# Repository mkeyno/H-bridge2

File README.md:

# H-bridge2
this is H-bridge circuit to operate under 12-24 input voltage, with parallel mosfet and push-pull gate driver
##schematic of last change 

##PCB

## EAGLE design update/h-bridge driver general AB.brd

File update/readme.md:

new updated file has been added

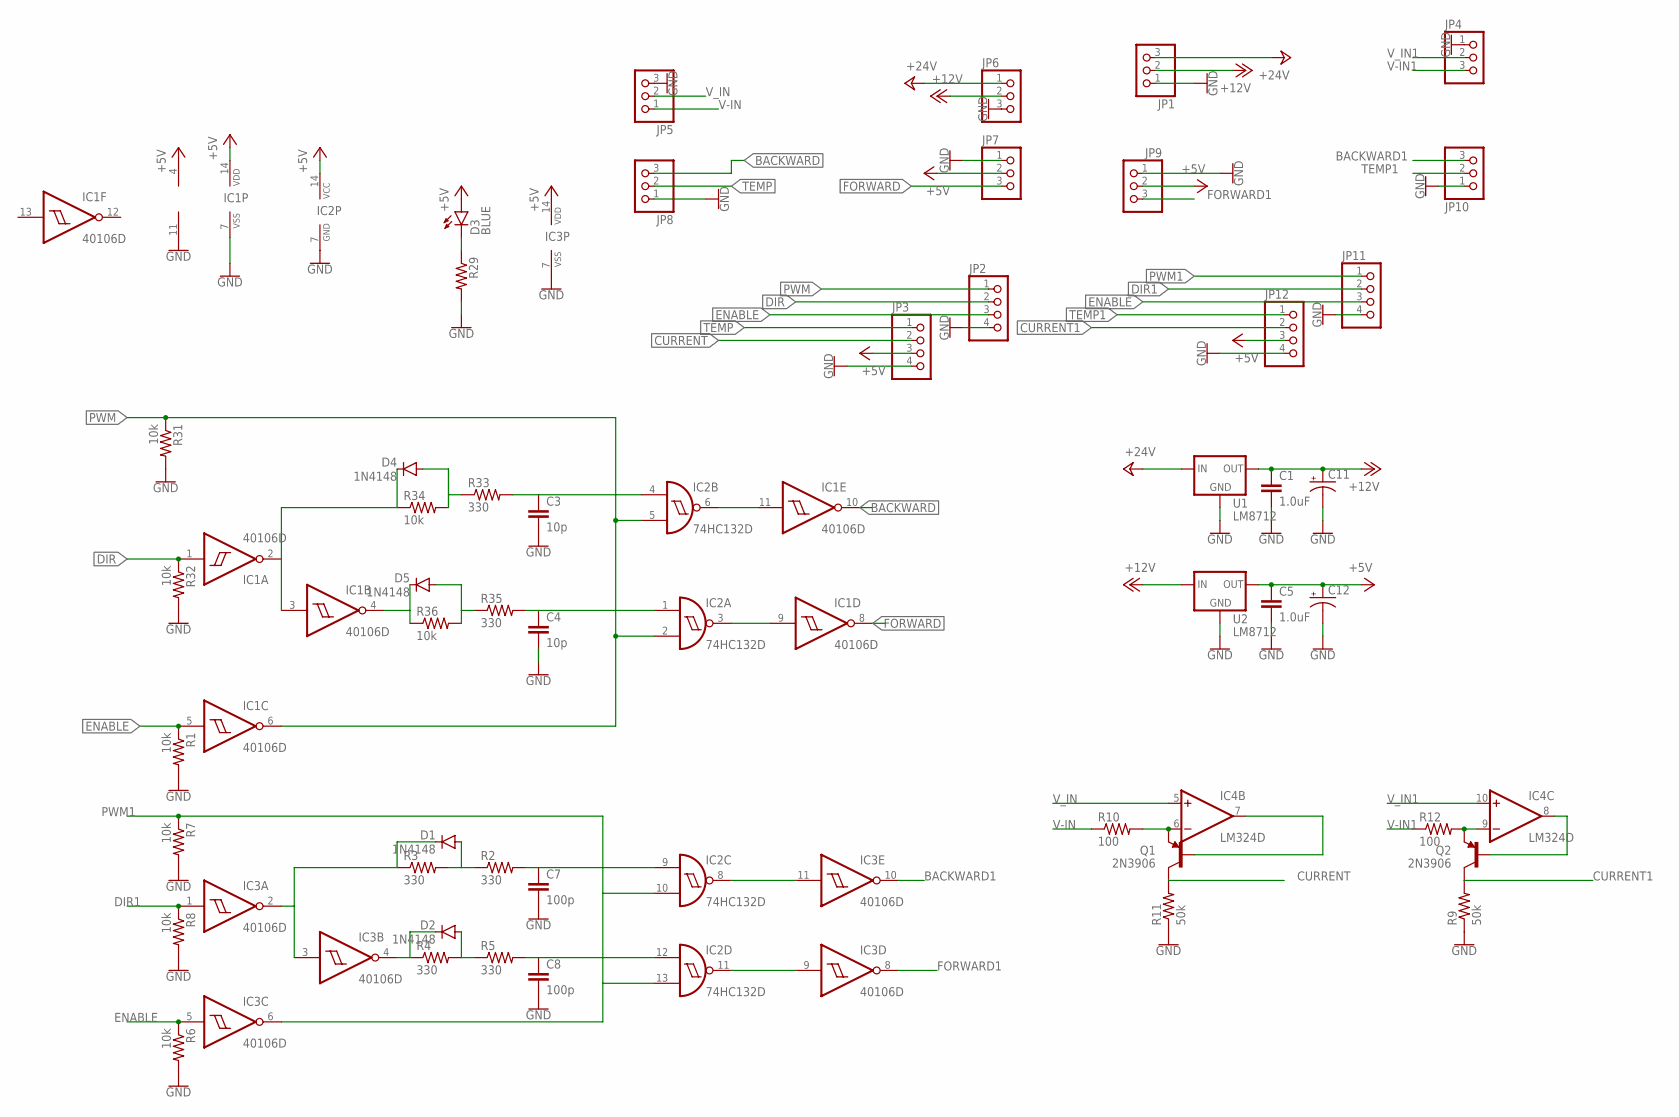
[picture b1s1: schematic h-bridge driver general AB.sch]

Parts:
C1, C5: 1.0uF; 1206
C3, C4: 10p; 0805-CAP
C7, C8: 100p; 0805-CAP
C11, C12: CAP_POLPTH4; CPOL-RADIAL-1000UF-25V
D1, D2, D4, D5: 1N4148; SOD-123
D3: BLUE; LED-1206
IC1, IC3: 40106D; SO14
IC2: 74HC132D; SO14
IC4: LM324D; SO14
JP1, JP4, JP5, JP6, JP7, JP8, JP9, JP10: PINHD-1X3; 1X03
JP2, JP3, JP11, JP12: PINHD-1X4; 1X04
Q1, Q2: 2N3906; SOT23-3
R1, R6, R7, R8, R31, R32, R34, R36: 10k; 0805
R2, R3, R4, R5, R33, R35: 330; 0805
R9, R11: 50k; 0805
R10, R12: 100; 0805
R29: 0.3OHM-1/8W-1%(0805); 0805
U1, U2: LM8712; 78XXL

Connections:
+5V: C5.1, C12.+, D3.A, IC1.14 (VDD), IC2.14 (VCC), IC3.14 (VDD), IC4.4 (V+), JP3.3, JP7.2, JP9.2, JP12.3, U2.OUT
+12V: C1.1, C11.+, JP1.2, JP6.2, U1.OUT, U2.IN
+24V: JP1.3, JP6.1, U1.IN
BACKWARD: IC1.10 (O), JP8.3
BACKWARD1: IC3.10 (O), JP10.3
CURRENT: JP3.2, Q1.3 (C), R11.2
CURRENT1: JP12.2, Q2.3 (C), R9.2
DIR: IC1.1 (I), JP2.2, R32.1
DIR1: IC3.1 (I), JP11.2, R8.1
ENABLE: IC1.5 (I), IC3.5 (I), JP2.3, JP11.3, R1.1, R6.1
FORWARD: IC1.8 (O), JP7.3
FORWARD1: IC3.8 (O), JP9.3
GND: C1.2, C3.2, C4.2, C5.2, C7.2, C8.2, C11.-, C12.-, IC1.7 (VSS), IC2.7 (GND), IC3.7 (VSS), IC4.11 (V-), JP1.1, JP2.4, JP3.4, JP4.1, JP5.3, JP6.3, JP7.1, JP8.1, JP9.1, JP10.1, JP11.4, JP12.4, R1.2, R6.2, R7.2, R8.2, R9.1, R11.1, R29.2, R31.2, R32.2, U1.GND, U2.GND
unnamed: IC1.11 (I), IC2.6 (O)
unnamed: IC1.9 (I), IC2.3 (O)
unnamed: IC2.8 (O), IC3.11 (I)
unnamed: IC2.11 (O), IC3.9 (I)
unnamed: C7.1, IC2.9 (I0), R2.2
unnamed: D3.C, R29.1
unnamed: D1.A, R2.1, R3.2
unnamed: D1.C, IC3.2 (O), IC3.3 (I), R3.1
unnamed: IC4.6 (-IN), Q1.2 (E), R10.2
unnamed: D2.C, IC3.4 (O), R4.1
unnamed: D2.A, R4.2, R5.1
unnamed: C8.1, IC2.12 (I0), R5.2
unnamed: IC4.7 (OUT), Q1.1 (B)
unnamed: IC4.9 (-IN), Q2.2 (E), R12.2
unnamed: IC4.8 (OUT), Q2.1 (B)
unnamed: D4.C, IC1.2 (O), IC1.3 (I), R34.1
unnamed: D4.A, R33.1, R34.2
unnamed: C3.1, IC2.4 (I0), R33.2
unnamed: C4.1, IC2.1 (I0), R35.2
unnamed: D5.A, R35.1, R36.2
unnamed: D5.C, IC1.4 (O), R36.1
PWM: IC1.6 (O), IC2.2 (I1), IC2.5 (I1), JP2.1, R31.1
PWM1: IC2.10 (I1), IC2.13 (I1), IC3.6 (O), JP11.1, R7.1
TEMP: JP3.1, JP8.2
TEMP1: JP10.2, JP12.1
V-IN: JP5.1, R10.1
V-IN1: JP4.3, R12.1
V_IN: IC4.5 (+IN), JP5.2
V_IN1: IC4.10 (+IN), JP4.2

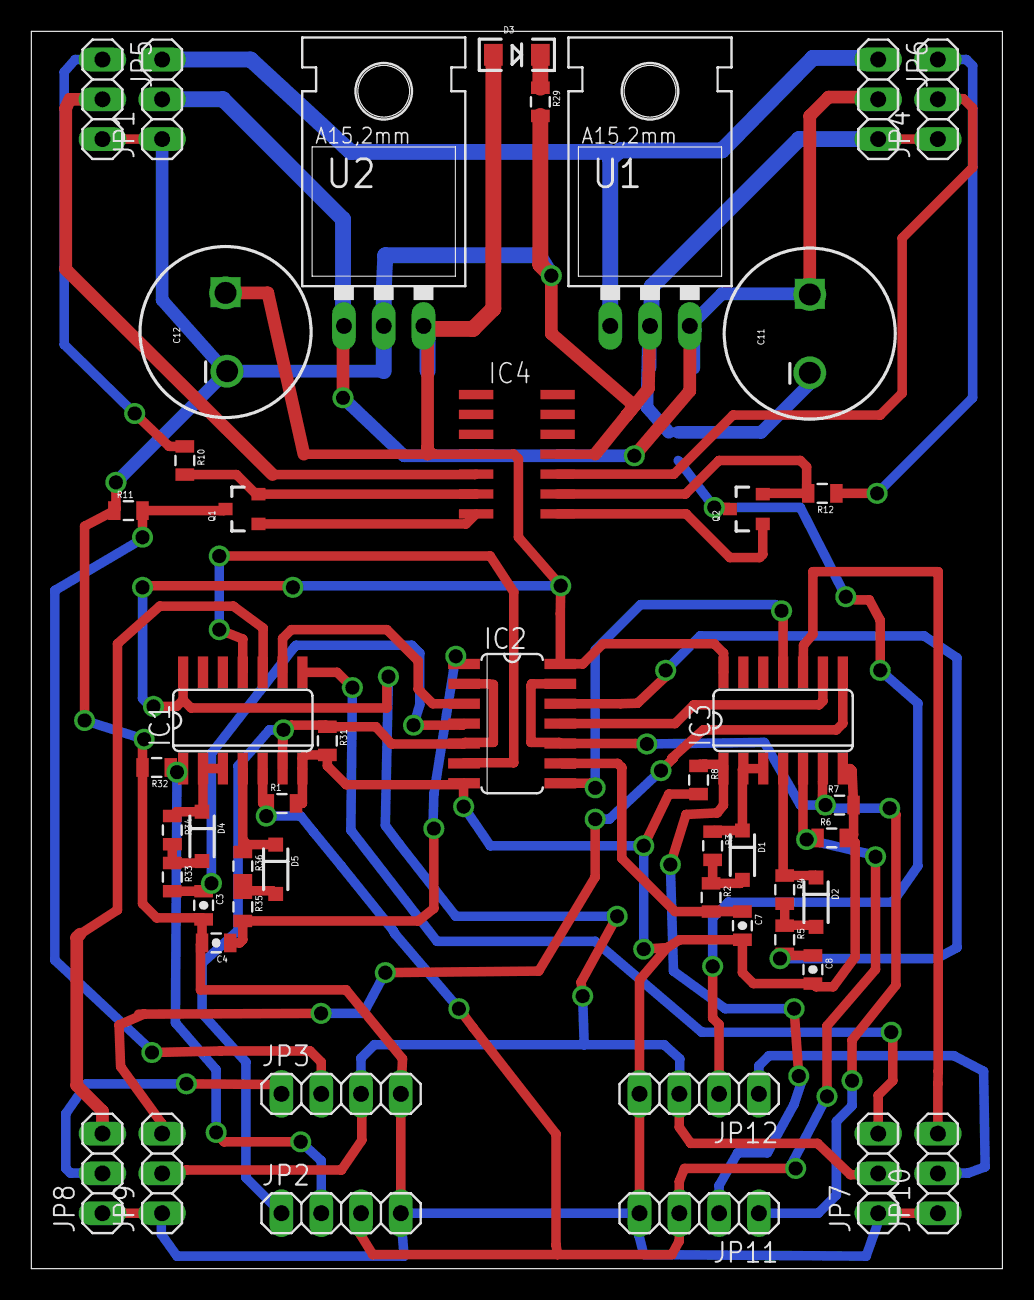
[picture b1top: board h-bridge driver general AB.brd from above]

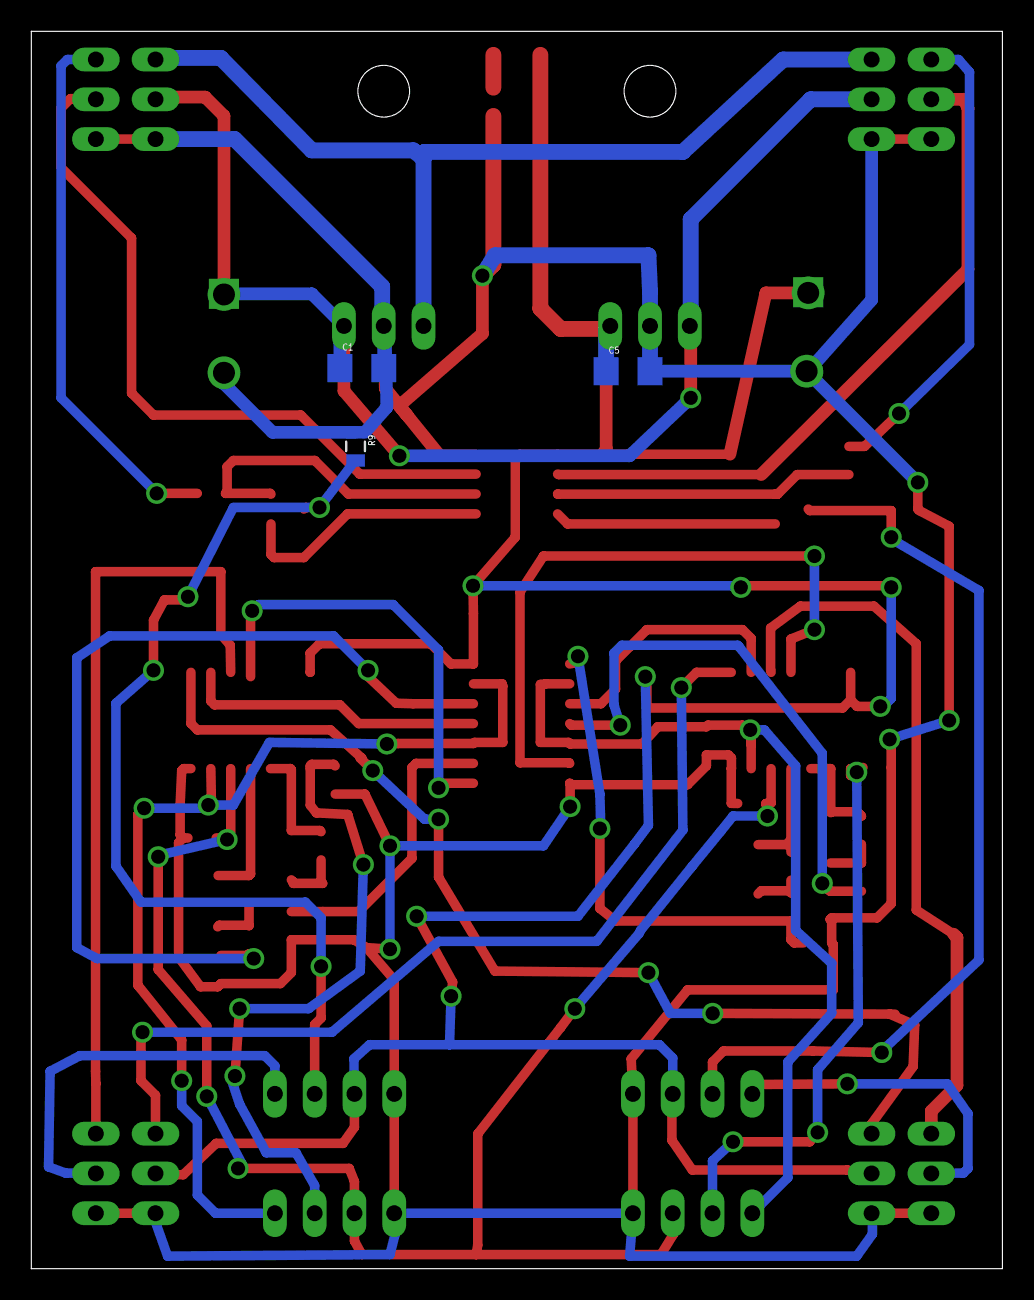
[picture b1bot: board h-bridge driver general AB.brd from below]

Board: 2 copper layers, 62.0 x 79.0 mm, 52 parts (3 on the bottom side), 42 nets.

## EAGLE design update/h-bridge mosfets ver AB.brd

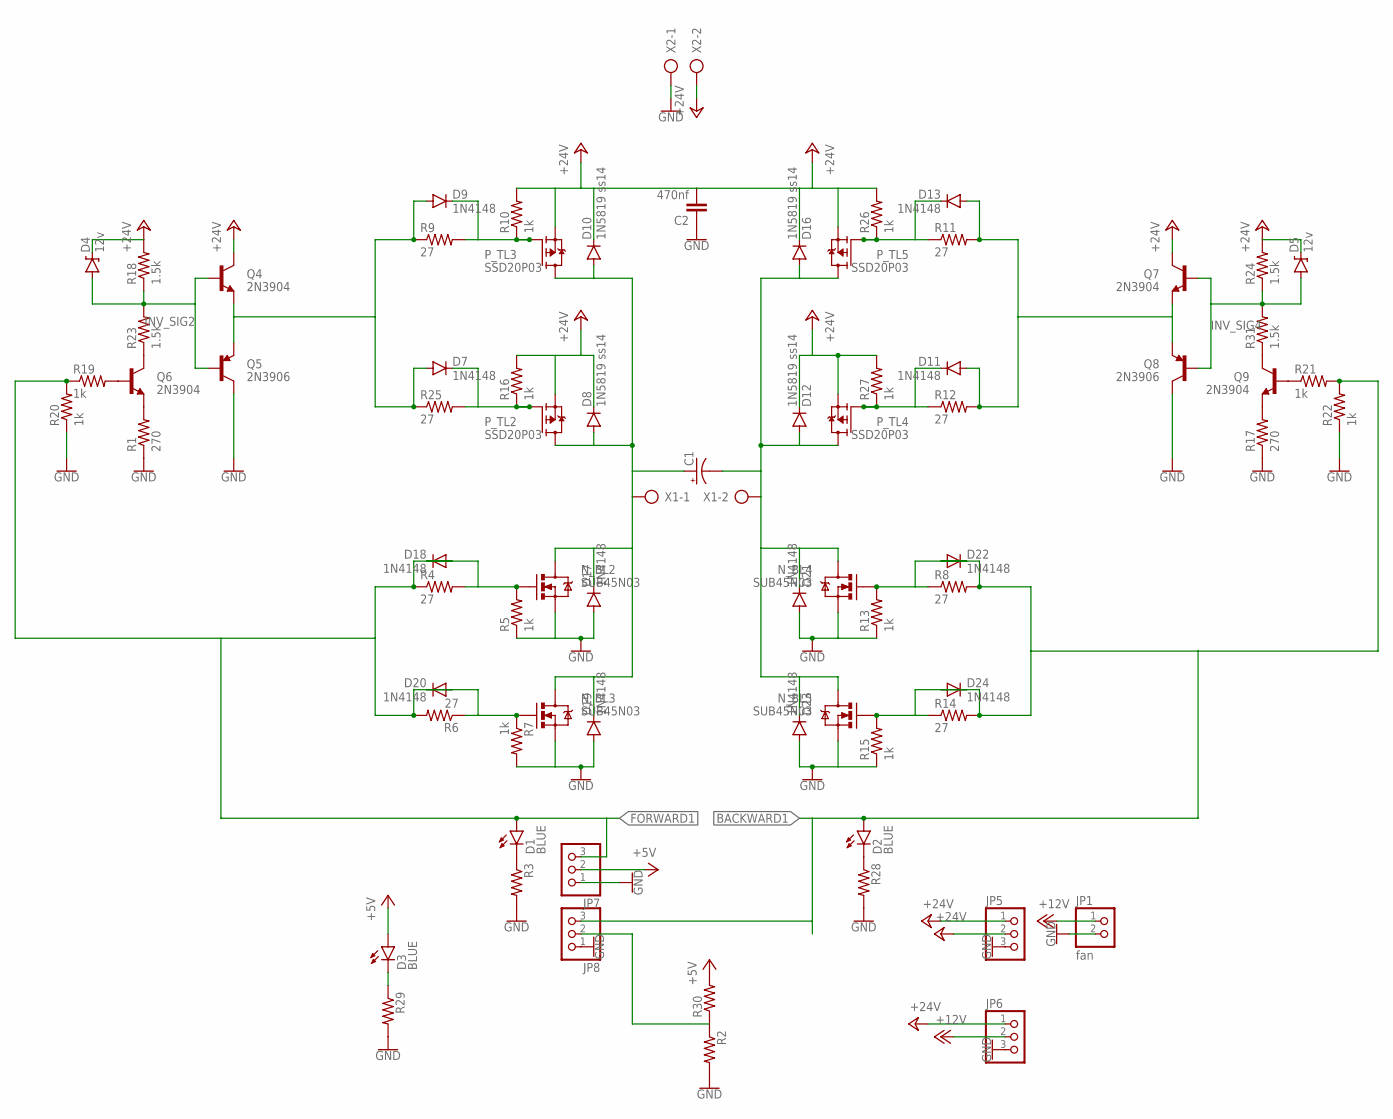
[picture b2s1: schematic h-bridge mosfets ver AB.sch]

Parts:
C1: 1000UF-25V(PTH); CPOL-RADIAL-1000UF-25V
C2: 470nf; 1206
D1, D2, D3: BLUE; LED-1206
D4, D5: 12v; SMB-DIODE
D7, D9, D11, D13, D17, D18, D19, D20, D21, D22, D23, D24: 1N4148; SOD-123
D8, D10, D12, D16: 1N5819 ss14; SOD-123
JP1: fan; 1X02
JP5, JP6, JP7, JP8: PINHD-1X3; 1X03
N_BL2, N_BL3, N_BL4, N_BL5: SUB45N03; TO-263/D2PAK
P_TL2, P_TL3, P_TL4, P_TL5: SSD20P03; TO252
Q4, Q6, Q7, Q9: 2N3904; SOT23-3
Q5, Q8: 2N3906; SOT23-3
R1, R17: 270; 0805
R2, R3, R28, R29: 0.3OHM-1/8W-1%(0805); 0805
R4, R6, R8, R9, R11, R12, R14, R25: 27; 0805
R5, R7, R10, R13, R15, R16, R19, R20, R21, R22, R26, R27: 1k; 0805
R18, R23, R24, R31: 1.5k; 0805
R30: RESISTORPTH-1/4W-VERT-KIT; AXIAL-0.1EZ
X1, X2: AK300/2

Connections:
+5V: D3.A, JP7.2, R30.P$2 (2)
+12V: JP1.1, JP6.2
+24V: C2.2, D4.C, D5.C, D8.C, D10.C, D12.C, D16.C, JP5.1, JP5.2, JP6.1, P_TL2.2 (S), P_TL3.2 (S), P_TL4.2 (S), P_TL5.2 (S), Q4.3 (C), Q7.3 (C), R10.2, R16.2, R18.2, R24.2, R26.2, R27.2, X2.2
BACKWARD1: D2.A, D22.A, D24.A, JP8.3, R8.2, R14.2, R21.2, R22.2
DR2: D11.A, D13.A, Q7.2 (E), Q8.2 (E), R11.2, R12.2
FORWARD1: D1.A, D18.A, D20.A, JP7.3, R4.1, R6.2, R19.1, R20.2
GND: C2.1, D17.A, D19.A, D21.A, D23.A, JP1.2, JP5.3, JP6.3, JP7.1, JP8.1, N_BL2.3 (S), N_BL3.3 (S), N_BL4.3 (S), N_BL5.3 (S), Q5.3 (C), Q8.3 (C), R1.1, R2.2, R3.2, R5.1, R7.2, R13.1, R15.1, R17.1, R20.1, R22.1, R28.2, R29.2, X2.1
INV_SIG2: D4.A, Q4.1 (B), Q5.1 (B), R18.1, R23.2
INV_SIG4: D5.A, Q7.1 (B), Q8.1 (B), R24.1, R31.2
LEFT: C1.-, D12.A, D16.A, D21.C, D23.C, N_BL4.2 (D), N_BL5.2 (D), P_TL4.3 (D), P_TL5.3 (D), X1.2
unnamed: Q6.2 (E), R1.2
unnamed: Q6.1 (B), R19.2
unnamed: Q9.1 (B), R21.1
unnamed: Q9.2 (E), R17.2
unnamed: D1.C, R3.1
unnamed: D2.C, R28.1
unnamed: D3.C, R29.1
unnamed: D7.C, P_TL2.1 (G), R16.1, R25.2
unnamed: D20.C, N_BL3.1 (G), R6.1, R7.1
unnamed: JP8.2, R2.1, R30.P$1 (1)
unnamed: D9.C, P_TL3.1 (G), R9.2, R10.1
unnamed: D22.C, N_BL4.1 (G), R8.1, R13.2
unnamed: Q6.3 (C), R23.1
unnamed: D11.C, P_TL4.1 (G), R12.1, R27.1
unnamed: Q9.3 (C), R31.1
unnamed: D13.C, P_TL5.1 (G), R11.1, R26.1
unnamed: D7.A, D9.A, Q4.2 (E), Q5.2 (E), R9.1, R25.1
unnamed: D18.C, N_BL2.1 (G), R4.2, R5.2
unnamed: D24.C, N_BL5.1 (G), R14.1, R15.2
RIGHT: C1.+, D8.A, D10.A, D17.C, D19.C, N_BL2.2 (D), N_BL3.2 (D), P_TL2.3 (D), P_TL3.3 (D), X1.1

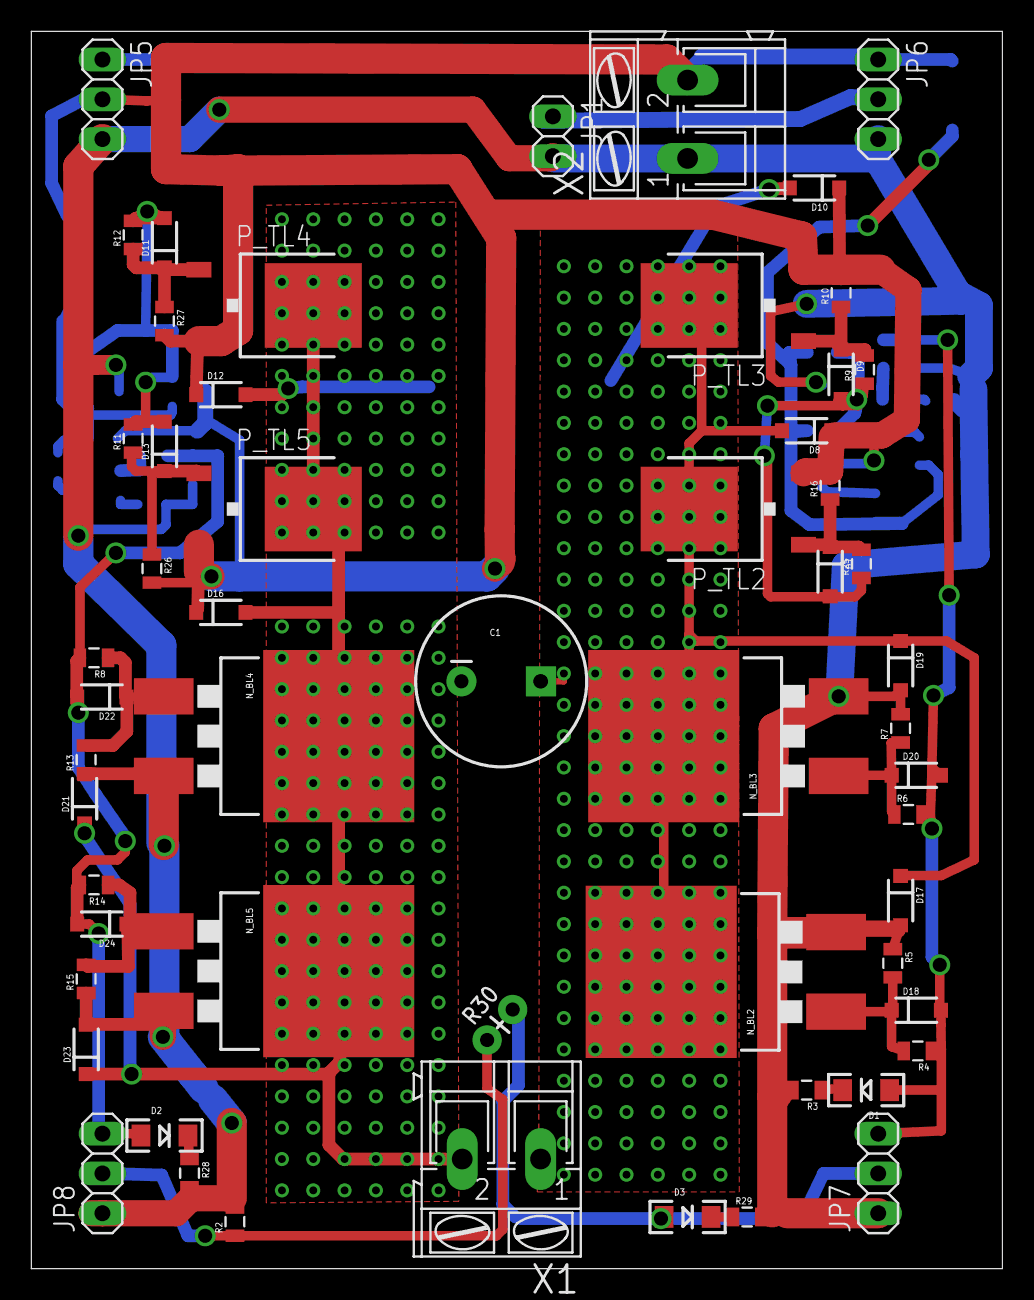
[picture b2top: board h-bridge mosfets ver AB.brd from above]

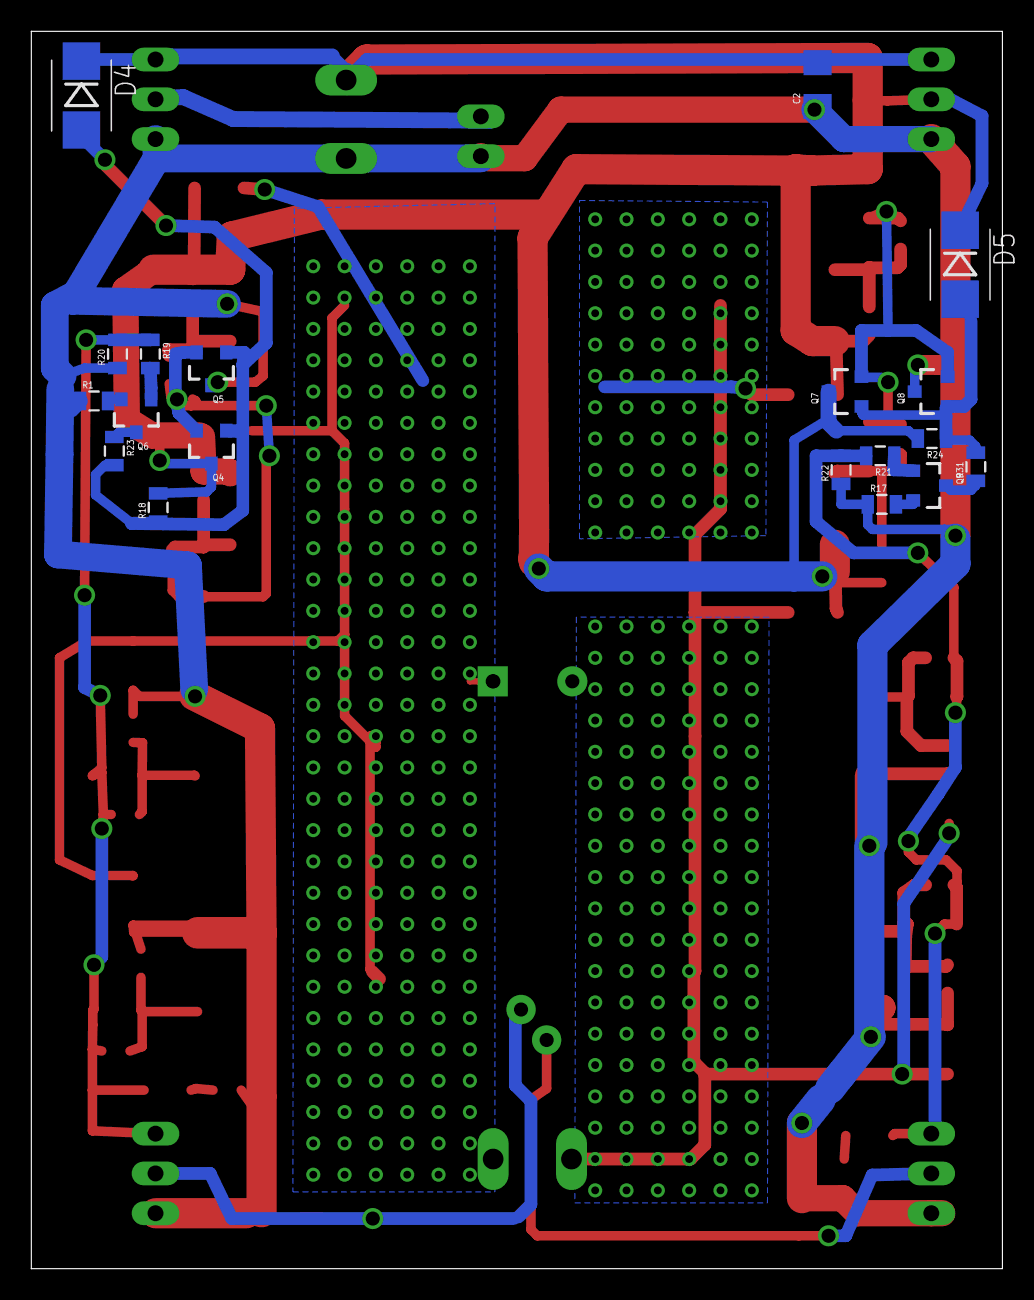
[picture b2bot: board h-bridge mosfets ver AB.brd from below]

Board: 2 copper layers, 62.0 x 79.0 mm, 75 parts (19 on the bottom side), 30 nets.

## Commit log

2018-09-13 schematic of H-bridge with parallel mosfet and push-pull gate driver
2018-09-13 12v line remove and DIODE-ZENER 12v added
2018-09-18 driver pcb
2018-09-18 power mosfet board
2018-09-18 NAND gate driver
2019-06-27 updated circuit

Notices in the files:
parts and their libraries:
SparkFun-Capacitors: Licensing: Creative Commons ShareAlike 4.0 International - https://creativecommons.org/licenses/by-sa/4.0
